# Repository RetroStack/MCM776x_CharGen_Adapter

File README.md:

# MCM667x Character Generator Adapter

This repository provides an adapter for the Motorola MCM6670 and related (MCM667x series) character generators for vintage computers. ROMs with various character sets are provided in a [separate repository](https://github.com/RetroStack/Character_Generator_ROMs).
The entire project is available under the MIT license.

## Project Details

### Latest Files

In the "Latest" folder, you'll find the most up-to-date design files, including:

- Gerber files suitable for popular online PCB manufacturers like [PCBWay](/Latest/MCM776x_Character_Generator_Adapter_Gerber_PCBWay.zip) and [JLCPCB](/Latest/MCM776x_Character_Generator_Adapter_Gerber_JLCPCB.zip). Most manufacturers should be fine with either.
- A Bill of Materials (BOM) in both [CSV](/Latest/MCM776x_Character_Generator_Adapter_BOM.csv) (with sources) and [PDF](/Latest/MCM776x_Character_Generator_Adapter_BOM.pdf) formats.
- Layers exported in PDF format.
- The [full schematics](/Latest/MCM776x_Character_Generator_Adapter_Schematics.pdf) of the adapter.

### Implementation

The adapter has been implemented using KiCAD 7. The KiCAD project files are included in this repository.

### Assembly Instructions

1) Get a straight male pin header with pitch (2.54mm; standard) and break it to a 9-pin length. Do this twice. A machined header is recommended if the adapter will be inserted into a socket. Inserting a square pin in a socket might damage them.
2) Solder the pins in place into the central lengthwise holes. To align them correctly, you can use another socket or a breadboard. Stick the longer parts into the socket/breadboard and put the PCB on top. Solder first both edges on each. Recheck if they are flush to the header. If not, reheat the corner that needs correction and press down on PCB until flush. Then, solder all other pins.
3) Install the resistor network. One edge has a square around one pin. This should be where pin 1 will be inserted. Pin 1 is identified on the resistor network usually with a dot.
4) Write/burn one of the binaries for character sets onto a ROM.
5) (Optional) Solder a socket in place. Similarly to the headers mentioned above, only solder one pin on each side before soldering all to be able to make adjustments as needed. Adding a socket is not recommended for machines which do not have enough space for it (e.g., TRS-80 Model 1). For these, you need to skip this step and solder the ROM directly to the board.
6) Solder the ROM to the board or insert it into the socket.

The adapter provides various configurations. Depending on your ROM used, only some PINs can be configured. See the description on the board for more details.
For example, a 27256 ROM only uses 14 pins and therefore only 5 pins can be configured. The 6th will not have an affect.

**NOTE**: Keep in mind that the bits are active-low. That means if you want to put set a 1 on a specific address, you leave it unbridged. If you want a 0, then bridge it. This can be fixed by using a reversed/inverted ROM. See below for more details why that is.

**NOTE**: The board exposes the bits from right to left. If you prefer left to right (e.g. for DIP switches to match labels), then flip the address bits in the ROM or use the provided "f" versions of these.

Here are some examples:

#### No Configuration
7) Clip off extension board on perforated line.
8) Use solder bridges on the bottom to pre-select a character set. 

#### Jumper Caps
7) Add a 2 row pin straight header (2.54mm pitch) to the center two pins of the extension board. You need to leave one row on each side (on edge and on the side next to the ROM).
8) Add jumpers.

### Right Angle Jumpers
**NOTE**: Due to space constraints, only 5 jumpers can be used.
7) Clip off extension board on perforated line.
8) Add a 2 row pin right-angle header (2.54mm pitch) to the bottom of the PCB, extending one end out over the board where the extension was.
8) Add jumpers.

### DIP Switches
**NOTE**: For TRS-80 Model 1: Use low-profile dip switches to make sure the adapter fits in the case.
7) Add a DIP switch on the extension board. The DIP switch should cover all holes from front to back.

### DIP Switches on extension board
**NOTE**: Due to space constraints, only 5 DIP switches can be used.
7) Clip off extension board on perforated line.
8) Solder up to 6 wires (e.g. ribbon cable) to the bottom of the PCB. Use up to 5 wires for each address line, which is the row close to the center of the board (next to the revision number). To identify which address line is which, see the label just below the ROM on the top of the adapter PCB. Solder at least one wire to any of the holes closer to the edge of the board. These are ground pins and therefore any could be used.
9) Solder all wires to the extension board. Use the central two rows of holes. Solder it on from the bottom as DIP switches will be added to the top. Solder the address lines closest to the perforated line where the extension board was attached to the adapter PCB. Solder the single ground wire to and other hole of the second row of holes further away from the perforated edge.
10) Add a DIP switch on the extension board. The DIP switch should cover all holes from front to back. You may need to trim the soldered pins of the cable to solder the DIP switches as close to flush as possible.

### Jumper caps on extension board
NOTE: Due to space constraints, only 5 jumpers can be used.
7) Clip off extension board on perforated line.
8) Solder up to 6 wires (e.g. ribbon cable) to the bottom of the PCB. Use up to 5 wires for each address line, which is the row close to the center of the board (next to the revision number). To identify which address line is which, see the label just below the ROM on the top of the adapter PCB. Solder at least one wire to any of the holes closer to the edge of the board. These are ground pins and therefore any could be used.
9) Add a 2 row pin straight header (2.54mm pitch) to the center two pins of the extension board. You need to leave one row on each side (on edge and on the side next to the ROM).
10) Solder all wires to the extension board. Use the row closer to the perforated edge to solder the address lines. Solder the single ground wire to and other hole at the bottom edge furthest away from the perforated edge. You can solder it from the top or bottom.
11) Add jumpers.

### Why is the configuration active low?
Some ROMs, especially the EEPROMs have an active-low WRITE pin that needs to be HIGH (or 1) in normal (read) use. To avoid putting ROMs in an incorrect mode (write mode instead of read mode), all additional pins are pulled high by default through pull-up resistors.

### Why are address lines from right to left?
Having them in this orientation was the simplest without adding complexity to the design. Additionally, the addressing depends on what type of configuration you use. Binary numbers are usually written from right to left (as implemented) and this works best for jumpers, for example. However, DIP switches uses labels from left to right.
Overall, one direction had to be chosen, and I went with the simplest. This can be fixed by flipping the address bits. ROMs having this fix already marked with an "f".

### Bill of Materials (BOM)

Below is a list of materials needed to assemble a complete system. Please note that the links and prices (scroll to the right to see them; as of March 3rd, 2024) will not be updated in the future and should only be used as a reference for locating the correct items.

**NOTE**: Links and alternatives are provided to assist you in finding the necessary components. I cannot guarantee the complete accuracy or reliability of all these links and alternatives. Please check it for yourself!

|PCB REFERENCE|QTY|VALUE|COMMENT|EACH|TOTAL|SOURCE LINK|
|-|-|-|-|-|-|-|
|RN1|1|4.7k Ohm|6 resistor network with 7-pins, bussed resistors|0.5|0.5|[Mouser](https://www.mouser.com/ProductDetail/652-4607X-1LF-4.7K)|
|U1|2||Source Link is for a rather expensive version of a machined straight male pin header with 40-pins which can be broken into smaller pieces to server for both. There are cheaper ones, but the link is used for future reference.|1.0|1.0|[Mouser](https://www.amazon.com/ZYAMY-2-54mm-Breakable-Straight-Connector/dp/B0778KCHHR/)|
|U2|1|2x64-2x512|Examples are 23128, 23256, 2764, 27128, 27256, 27512, 2864, 28256 and all other variations such as 27C256 or AT28C64B|5.5|5.5|[Mouser](https://www.mouser.com/ProductDetail/556-AT28C64B15PU)|
|J1|1|-|Optional. Could be used for right-angle jumpers or attaching ribbon cable to move switch towards more accessible place.|1.02|1.02|[Mouser](https://www.mouser.com/ProductDetail/649-1012938294001BLF)|
|J2|1|-|Optional. Adding the ability to switch character sets.|0.27|0.27|[Mouser](https://www.mouser.com/ProductDetail/571-1033222)|
||1|Low-profile|Optional. Adding the ability to switch character sets.|0.67|0.67|[Mouser](https://www.mouser.com/ProductDetail/774-2105MS)|

### RetroStack Libraries

To work with this KiCAD project, you'll need the RetroStack libraries for KiCAD. Please [follow this link](https://www.github.com/RetroStack/KiCAD-Libraries) to access and install these libraries.

## Support this Project

RetroStack is passionate about exploring and preserving the legacy of older computer systems. My work involves creating detailed documentation and videos to share the knowledge. I am also dedicated to reviving these classic systems by reimplementing them and offering replacement parts at no cost. If you're keen on supporting this unique project, I invite you to visit my [Patreon page](https://www.patreon.com/RetroStack). Your support would be immensely valuable and greatly appreciated!

## License

This project is licensed under the MIT License - see the [LICENSE](LICENSE) file for details.

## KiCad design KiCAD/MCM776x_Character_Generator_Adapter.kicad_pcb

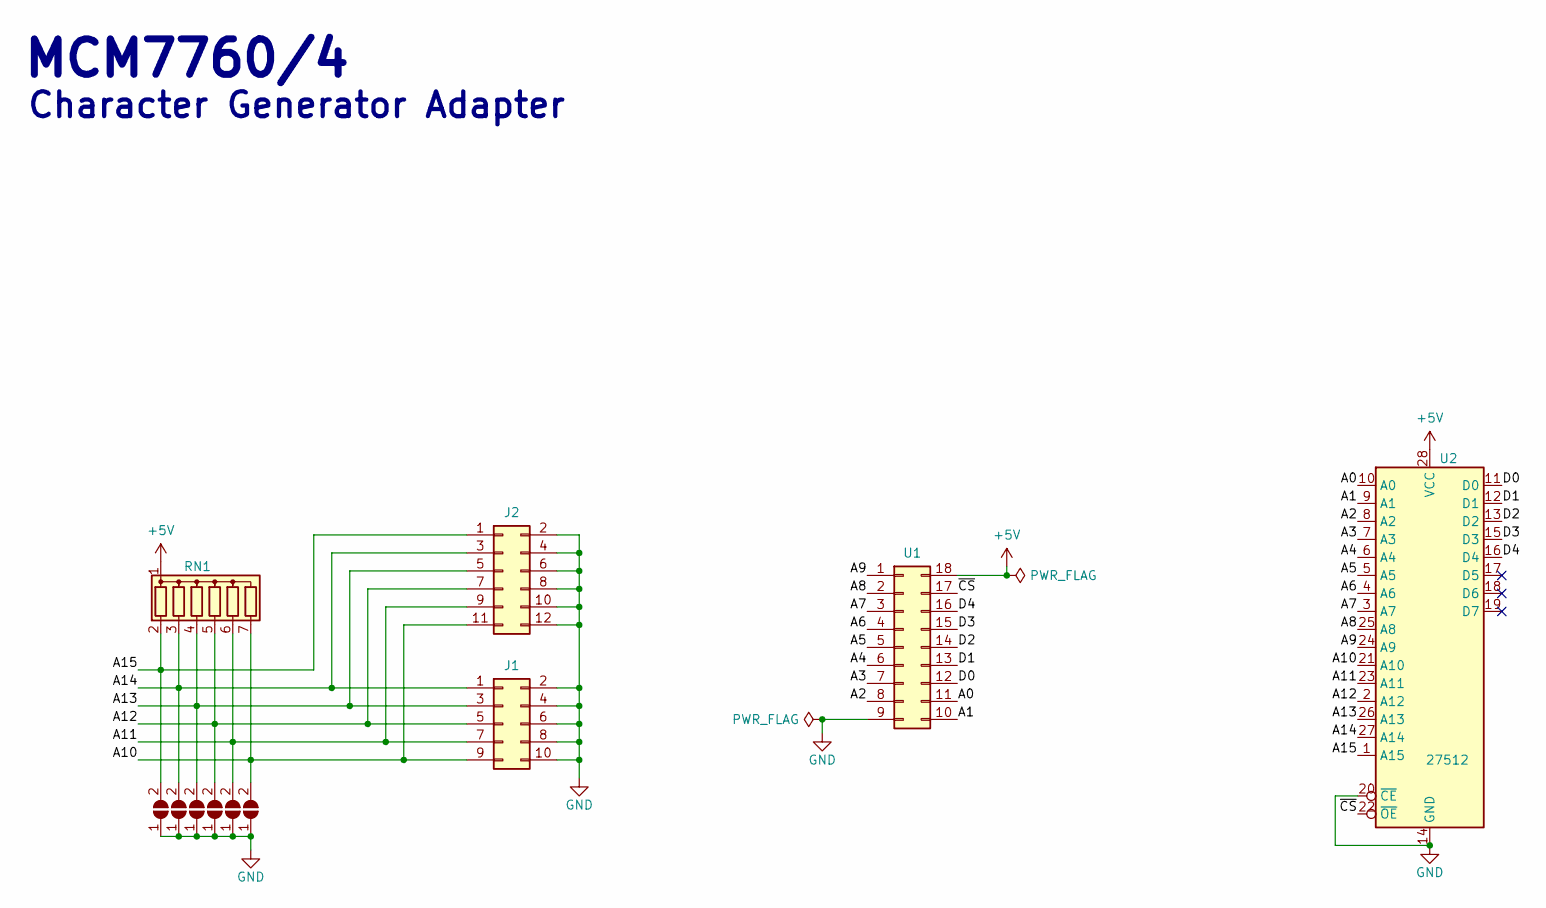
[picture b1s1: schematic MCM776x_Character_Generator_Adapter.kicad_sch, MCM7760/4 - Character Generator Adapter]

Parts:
J1: Conn_02x05_Odd_Even; PinHeader_2x05_P2.54mm_Vertical
J2: Conn_02x06_Odd_Even; DIPJumper_6
JP1, JP2, JP3, JP4, JP5, JP6: SolderJumper_2_Open; SolderJumper_2_Open_RoundedPad
RN1: R_Network06; R_Array_SIP7
U1: Conn_02x09_Counter_Clockwise; DIP-18_W7.62mm
U2: 27512; DIP-28_W15.24mm

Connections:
+5V: RN1.1 (common), U1.18, U2.28 (VCC)
/A0: U1.11, U2.10 (A0)
/A1: U1.10, U2.9 (A1)
/A2: U1.8, U2.8 (A2)
/A3: U1.7, U2.7 (A3)
/A4: U1.6, U2.6 (A4)
/A5: U1.5, U2.5 (A5)
/A6: U1.4, U2.4 (A6)
/A7: U1.3, U2.3 (A7)
/A8: U1.2, U2.25 (A8)
/A9: U1.1, U2.24 (A9)
/A10: J1.9, J2.11, JP6.2 (B), RN1.7 (R6), U2.21 (A10)
/A11: J1.7, J2.9, JP5.2 (B), RN1.6 (R5), U2.23 (A11)
/A12: J1.5, J2.7, JP4.2 (B), RN1.5 (R4), U2.2 (A12)
/A13: J1.3, J2.5, JP3.2 (B), RN1.4 (R3), U2.26 (A13)
/A14: J1.1, J2.3, JP2.2 (B), RN1.3 (R2), U2.27 (A14)
/A15: J2.1, JP1.2 (B), RN1.2 (R1), U2.1 (A15)
/D0: U1.12, U2.11 (D0)
/D1: U1.13, U2.12 (D1)
/D2: U1.14, U2.13 (D2)
/D3: U1.15, U2.15 (D3)
/D4: U1.16, U2.16 (D4)
/~CS: U1.17, U2.22 (~OE)
GND: J1.2, J1.4, J1.6, J1.8, J1.10, J2.2, J2.4, J2.6, J2.8, J2.10, J2.12, JP1.1 (A), JP2.1 (A), JP3.1 (A), JP4.1 (A), JP5.1 (A), JP6.1 (A), U1.9, U2.14 (GND), U2.20 (~CE)

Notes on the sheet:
MCM7760/4
Character Generator Adapter

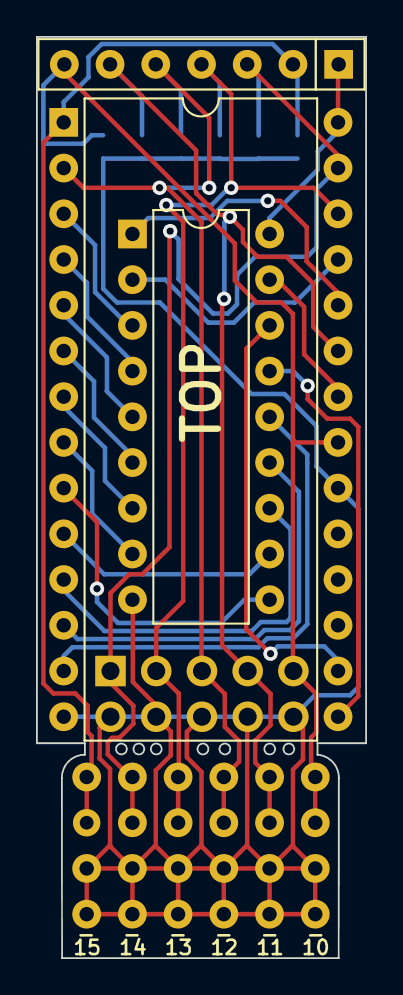
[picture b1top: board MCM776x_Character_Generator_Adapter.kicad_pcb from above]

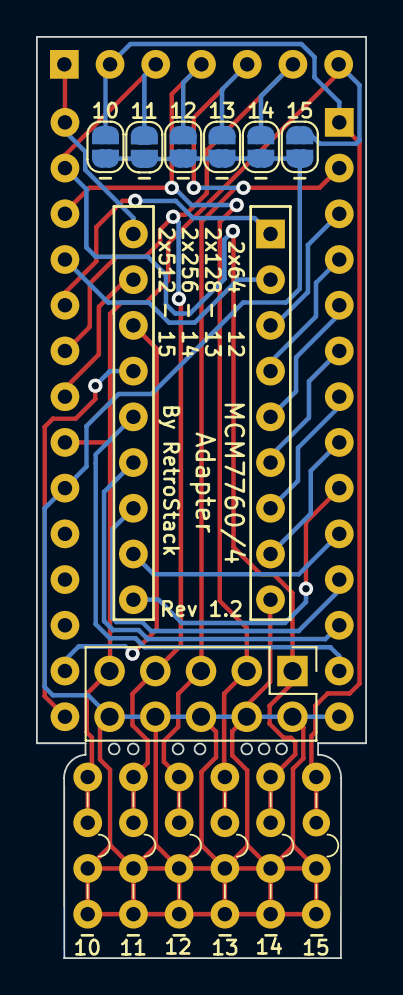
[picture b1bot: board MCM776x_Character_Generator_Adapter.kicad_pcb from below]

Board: 2 copper layers, 18.3 x 51.2 mm, 11 parts (8 on the bottom side), 24 nets.

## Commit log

2024-03-05 Add in-place photo
2024-03-06 Rev 1.1
2024-03-06 Rev 1.2
2024-05-20 Update LICENSE
2024-08-23 Upgrade to version 8
